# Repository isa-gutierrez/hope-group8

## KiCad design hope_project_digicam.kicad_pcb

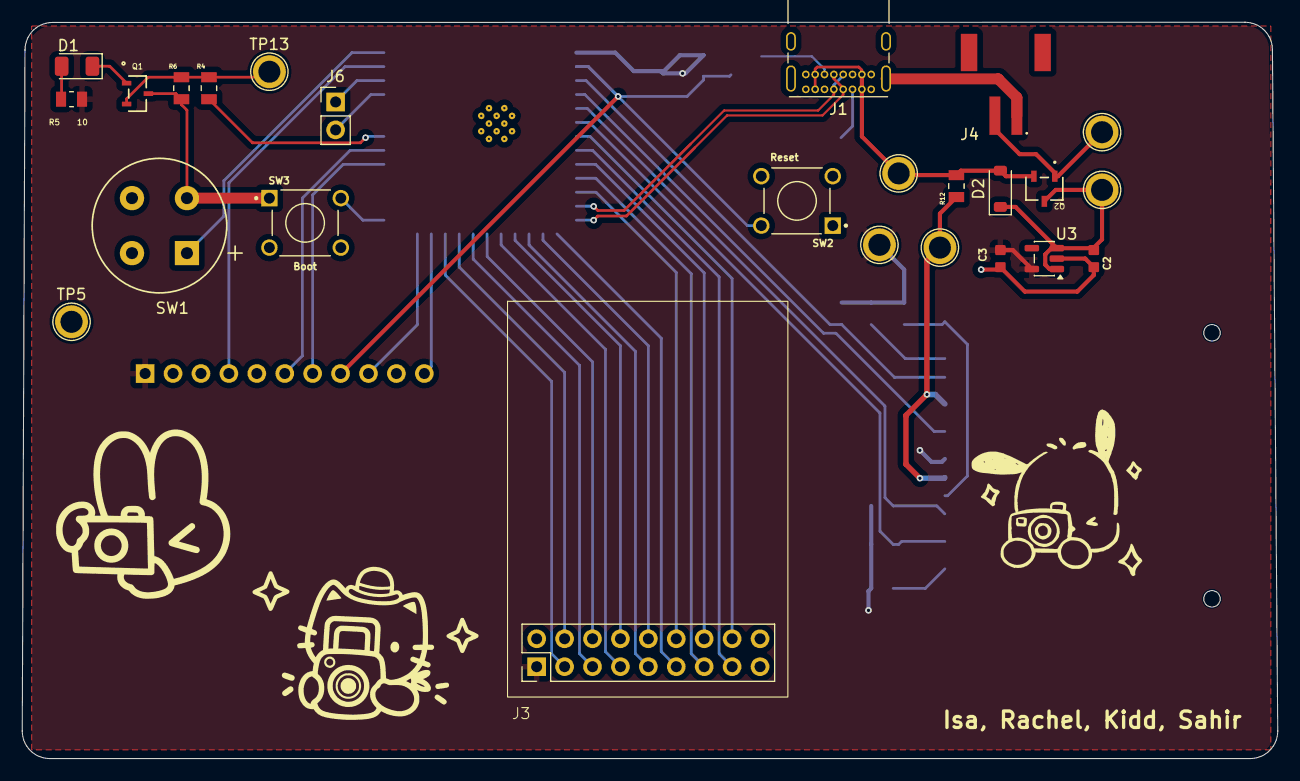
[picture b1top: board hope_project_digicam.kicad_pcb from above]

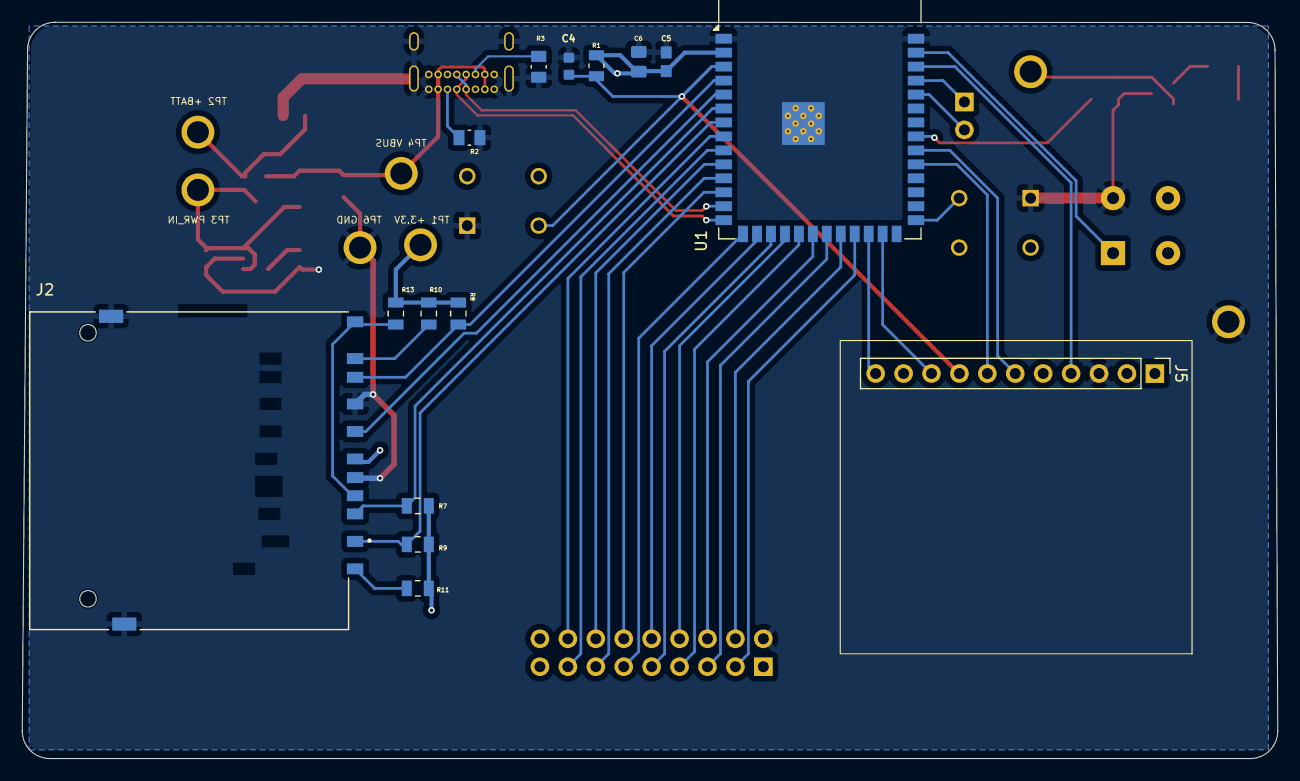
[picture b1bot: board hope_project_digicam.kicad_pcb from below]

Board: 2 copper layers, 114.2 x 67.0 mm, 40 parts (15 on the bottom side), 44 nets.

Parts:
C2, C3, C4: 1uF; 1uF_Cap
C5: 0.1uF; 0.1u_Cap
C6: 22uF; 22u_Cap
D1: LED; LED_1206_3216Metric
D2: D_Schottky; D_SOD-123
J1: USB_C_Receptacle_USB2.0_16P; USB_C_Receptacle_GCT_USB4085
J2: SD_Card_Port; SD_Card_Conn
J3: Camera_Pin_Out; Cam Module
J4: Lipo batt in; Right_Angle_Conn
J5: TFT_Pin_Socket; TFT Module
J6: extra; PinHeader_1x02_P2.54mm_Vertical
Q1: NMOS
Q2: PMOS
R1: 10k; 10_Res
R2, R3: 5.1k; 5.1k_Res
R4: 100; 100_Res
R5: 10; 10_Res
R6, R7, R8, R9, R10, R11, R13: 10k; 10k_Res
R12: 100k; 100k_Res
SW1: Cam Trigger; D6R_CNK
SW2: Reset; SW2_SW3
SW3: Boot; SW2_SW3
TP1 +3.3V, TP2 +BATT, TP3 PWR_IN, TP4 VBUS, TP5, TP6 GND, TP13: TestPoint; TestPoint_Plated_Hole_D2.0mm
U1: ESP32-S3-WROOM-1
U3: AP2112K-3.3; SOT-23-5

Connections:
+3.3V: C3.1, C5.1, C6.1, J2.4 (VDD), J3.1, J5.1, R1.1, R5.2, R7.1, R8.1, R9.1, R10.1, R11.1, R13.1, TP1 +3.3V.1, U1.2 (3V3), U3.5 (VOUT)
+BATT: J4.2, Q2.1 (D), TP2 +BATT.1
/CAM_D2: J3.16, U1.8 (IO15)
/CAM_D3: J3.15, U1.9 (IO16)
/CAM_D4: J3.14, U1.10 (IO17)
/CAM_D5: J3.13, U1.11 (IO18)
/CAM_D6: J3.12, U1.12 (IO8)
/CAM_D7: J3.11, U1.15 (IO3)
/CAM_D8: J3.10, U1.16 (IO46)
/CAM_D9: J3.9, U1.17 (IO9)
/CAM_HS: J3.6, U1.20 (IO12)
/CAM_PC: J3.7, U1.19 (IO11)
/CAM_SCL: J3.3, U1.23 (IO21)
/CAM_SDA: J3.4, U1.22 (IO14)
/CAM_TRIGGER: SW1.1, U1.39 (IO1)
/CAM_VS: J3.5, U1.21 (IO13)
/CAM_XC: J3.8, U1.18 (IO10)
/CC1: J1.A5 (CC1), R2.2
/CC2: J1.B5 (CC2), R3.2
/D+: J1.A6 (D+), J1.B6 (D+), U1.14 (USB_D+)
/D-: J1.A7 (D-), J1.B7 (D-), U1.13 (USB_D-)
/LED: R4.1, U1.33 (IO40)
/PWR_IN: C2.1, D2.1 (K), Q2.3 (S), TP3 PWR_IN.1, U3.1 (VIN), U3.3 (EN)
/SD_CS: J2.1 (DAT3/CD), R9.2, U1.7 (IO7)
/SD_DAT1: J2.8 (DAT1), R10.2
/SD_DAT2: J2.9 (DAT2), R11.2
/SD_MISO: J2.7 (DAT0), R8.2, U1.4 (IO4)
/SD_MOSI: J2.2 (CMD), R7.2, U1.6 (IO6)
/SD_SCK: J2.5 (CLK), U1.5 (IO5)
/TFT_CS: J5.7, U1.31 (IO38)
/TFT_DC: J5.9, U1.25 (IO48)
/TFT_LIT: J5.11, U1.24 (IO47)
/TFT_MOSI: J5.6, U1.32 (IO39)
/TFT_RST: C4.2, J5.8, R1.2, SW2.2, U1.3 (EN)
/TFT_SCK: J5.4, U1.38 (IO2)
/VBUS: D2.2 (A), J1.A4 (VBUS), J1.A9 (VBUS), J1.B4 (VBUS), J1.B9 (VBUS), Q2.2 (G), R12.2, TP4 VBUS.1
GND: C2.2, C3.2, C4.1, C5.2, C6.2, J1.A1 (GND), J1.A12 (GND), J1.B1 (GND), J1.B12 (GND), J1.S1 (SHIELD), J2.3 (VSS), J2.6 (VSS__1), J2.G1 (GND), J2.G2 (GND__1), J3.2, J4.1, J5.3, Q1.3 (S), R2.1, R3.1, R6.2, R12.1, SW1.2, SW2.1, SW3.1, TP5.1, TP6 GND.1, U1.1 (GND), U1.40 (GND), U1.41 (GND), U3.2 (GND)
unnamed: D1.2 (A), R5.1
unnamed: D1.1 (K), Q1.1 (D)
unnamed: J2.CD, J2.WP, R13.2
unnamed: J6.1, U1.37 (TXD0)
unnamed: J6.2, U1.36 (RXD0)
unnamed: Q1.2 (G), R4.2, R6.1, TP13.1
unnamed: SW3.2, U1.27 (IO0)

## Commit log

2026-03-12 added parts + started wiring
2026-03-16 finished schematic
2026-03-16 added test points
2026-04-02 layout progress
2026-04-03 fixed footprints
2026-04-03 pain au layoute
2026-04-03 plooh
2026-04-03 merging
2026-04-03 fixed footprints, laid stuff out, didn't route yet :(
2026-04-04 poured more stuff and tried moving components around
2026-04-09 finished layout pretty much
2026-04-10 made silkscreen more readable
